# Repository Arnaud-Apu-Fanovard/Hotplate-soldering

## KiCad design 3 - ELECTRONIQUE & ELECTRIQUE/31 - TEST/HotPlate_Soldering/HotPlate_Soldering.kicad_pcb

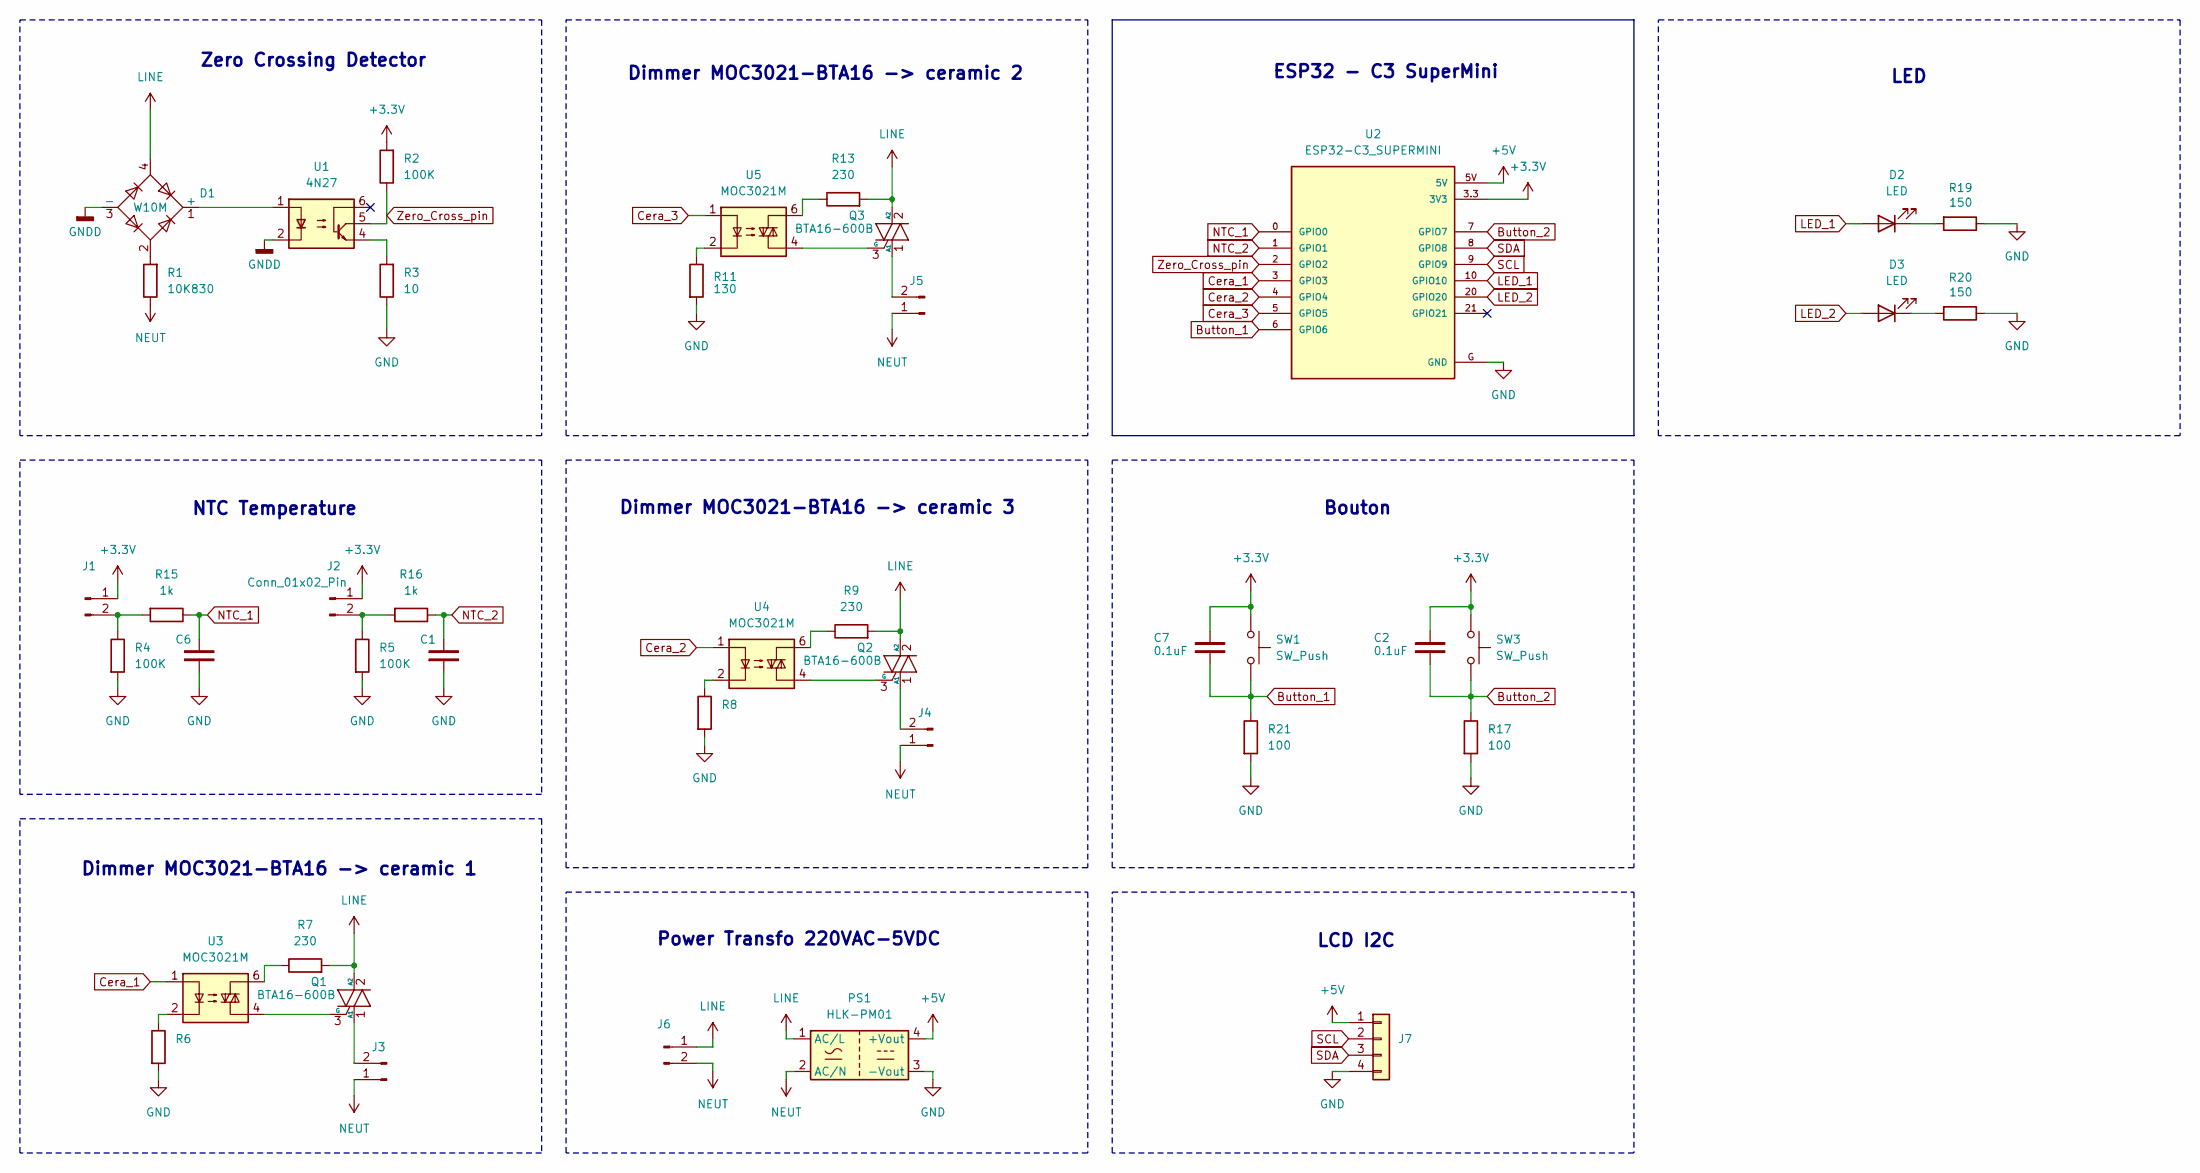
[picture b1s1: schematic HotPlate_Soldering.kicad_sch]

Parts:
C1, C6: 0.1; C_0805_2012Metric_Pad1.18x1.45mm_HandSolder
C2, C7: 0.1uF; C_0805_2012Metric_Pad1.18x1.45mm_HandSolder
D1: W10M; Diode_Bridge_Round_D9.8mm
D2, D3: LED; LED_D5.0mm
J1, J2: Conn_01x02_Pin; PinHeader_1x02_P2.54mm_Vertical
J3, J4, J5, J6: Conn_01x02_Pin; Samtec_HPM-02-01-x-S_Straight_1x02_Pitch5.08mm
J7: Conn_01x04; PinHeader_1x04_P2.54mm_Vertical
PS1: HLK-PM01; Converter_ACDC_Hi-Link_HLK-5Mxx
Q1, Q2, Q3: BTA16-600B; TO-220-3_Vertical
R1: 10K830; R_Axial_Power_L25.0mm_W6.4mm_P27.94mm
R2, R4, R5: 100K; R_0805_2012Metric
R3: 10; R_0805_2012Metric
R6, R8, R11: 130; R_0805_2012Metric
R7, R9, R13: 230; R_0805_2012Metric
R15, R16: 1k; R_0805_2012Metric
R17, R21: 100; R_0805_2012Metric
R19, R20: 150; R_0805_2012Metric_Pad1.20x1.40mm_HandSolder
SW1, SW3: SW_Push; SW_SPST_PTS645
U1: 4N27; DIP-6_W7.62mm
U2: ESP32-C3_SUPERMINI; MODULE_ESP32-C3_SUPERMINI
U3, U4, U5: MOC3021M; DIP-6_W7.62mm

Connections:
+3.3V: C2.2, C7.2, J1.1, J2.1, R2.2, SW1.1, SW3.1, U2.3.3 (3V3)
+5V: J7.1, PS1.4 (+Vout), U2.5V
Button_1: C7.1, R21.1, SW1.2, U2.6 (GPIO6)
Button_2: C2.1, R17.1, SW3.2, U2.7 (GPIO7)
Cera_1: U2.3 (GPIO3), U3.1
Cera_2: U2.4 (GPIO4), U4.1
Cera_3: U2.5 (GPIO5), U5.1
GND: C1.1, C6.1, J7.4, PS1.3 (-Vout), R3.1, R4.2, R5.2, R6.2, R8.2, R11.2, R17.2, R19.1, R20.1, R21.2, U2.G (GND)
GNDD: D1.3 (-), U1.2
LED_1: D2.2 (A), U2.10 (GPIO10)
LED_2: D3.2 (A), U2.20 (GPIO20)
LINE: D1.4, J6.1, PS1.1 (AC/L), Q1.2 (A2), Q2.2 (A2), Q3.2 (A2), R7.2, R9.2, R13.2
NEUT: J3.1, J4.1, J5.1, J6.2, PS1.2 (AC/N), R1.1
NTC_1: C6.2, R15.1, U2.0 (GPIO0)
NTC_2: C1.2, R16.1, U2.1 (GPIO1)
unnamed: D1.1 (+), U1.1
unnamed: D1.2, R1.2
unnamed: D2.1 (K), R19.2
unnamed: D3.1 (K), R20.2
unnamed: J1.2, R4.1, R15.2
unnamed: J2.2, R5.1, R16.2
unnamed: J3.2, Q1.1 (A1)
unnamed: J4.2, Q2.1 (A1)
unnamed: J5.2, Q3.1 (A1)
unnamed: Q1.3 (G), U3.4
unnamed: Q2.3 (G), U4.4
unnamed: Q3.3 (G), U5.4
unnamed: R3.2, U1.4
unnamed: R6.1, U3.2
unnamed: R7.1, U3.6
unnamed: R8.1, U4.2
unnamed: R9.1, U4.6
unnamed: R11.1, U5.2
unnamed: R13.1, U5.6
SCL: J7.2, U2.9 (GPIO9)
SDA: J7.3, U2.8 (GPIO8)
Zero_Cross_pin: R2.1, U1.5, U2.2 (GPIO2)

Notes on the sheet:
NTC Temperature
ESP32 - C3 SuperMini
Zero Crossing Detector
Dimmer MOC3021-BTA16 -> ceramic 3
LED
Power Transfo 220VAC-5VDC
Dimmer MOC3021-BTA16 -> ceramic 1
Dimmer MOC3021-BTA16 -> ceramic 2
LCD I2C
Bouton

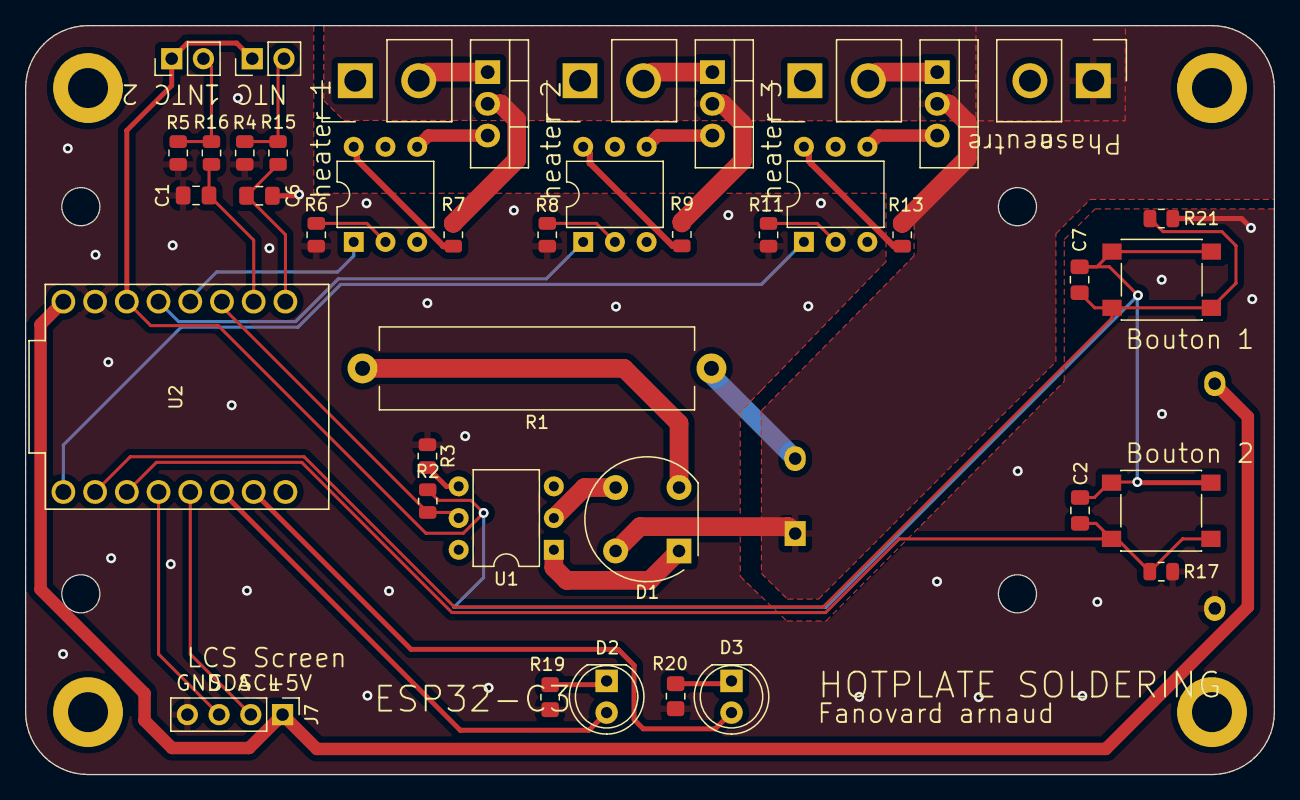
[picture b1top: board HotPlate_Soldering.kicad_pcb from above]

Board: 2 copper layers, 100.0 x 60.0 mm, 42 parts (1 on the bottom side), 37 nets.

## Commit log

2025-01-17 Commit_0.0 Creation of folders and add the existant project
